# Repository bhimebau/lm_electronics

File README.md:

# lm_electronics
Light monitor device for hoosier national forest

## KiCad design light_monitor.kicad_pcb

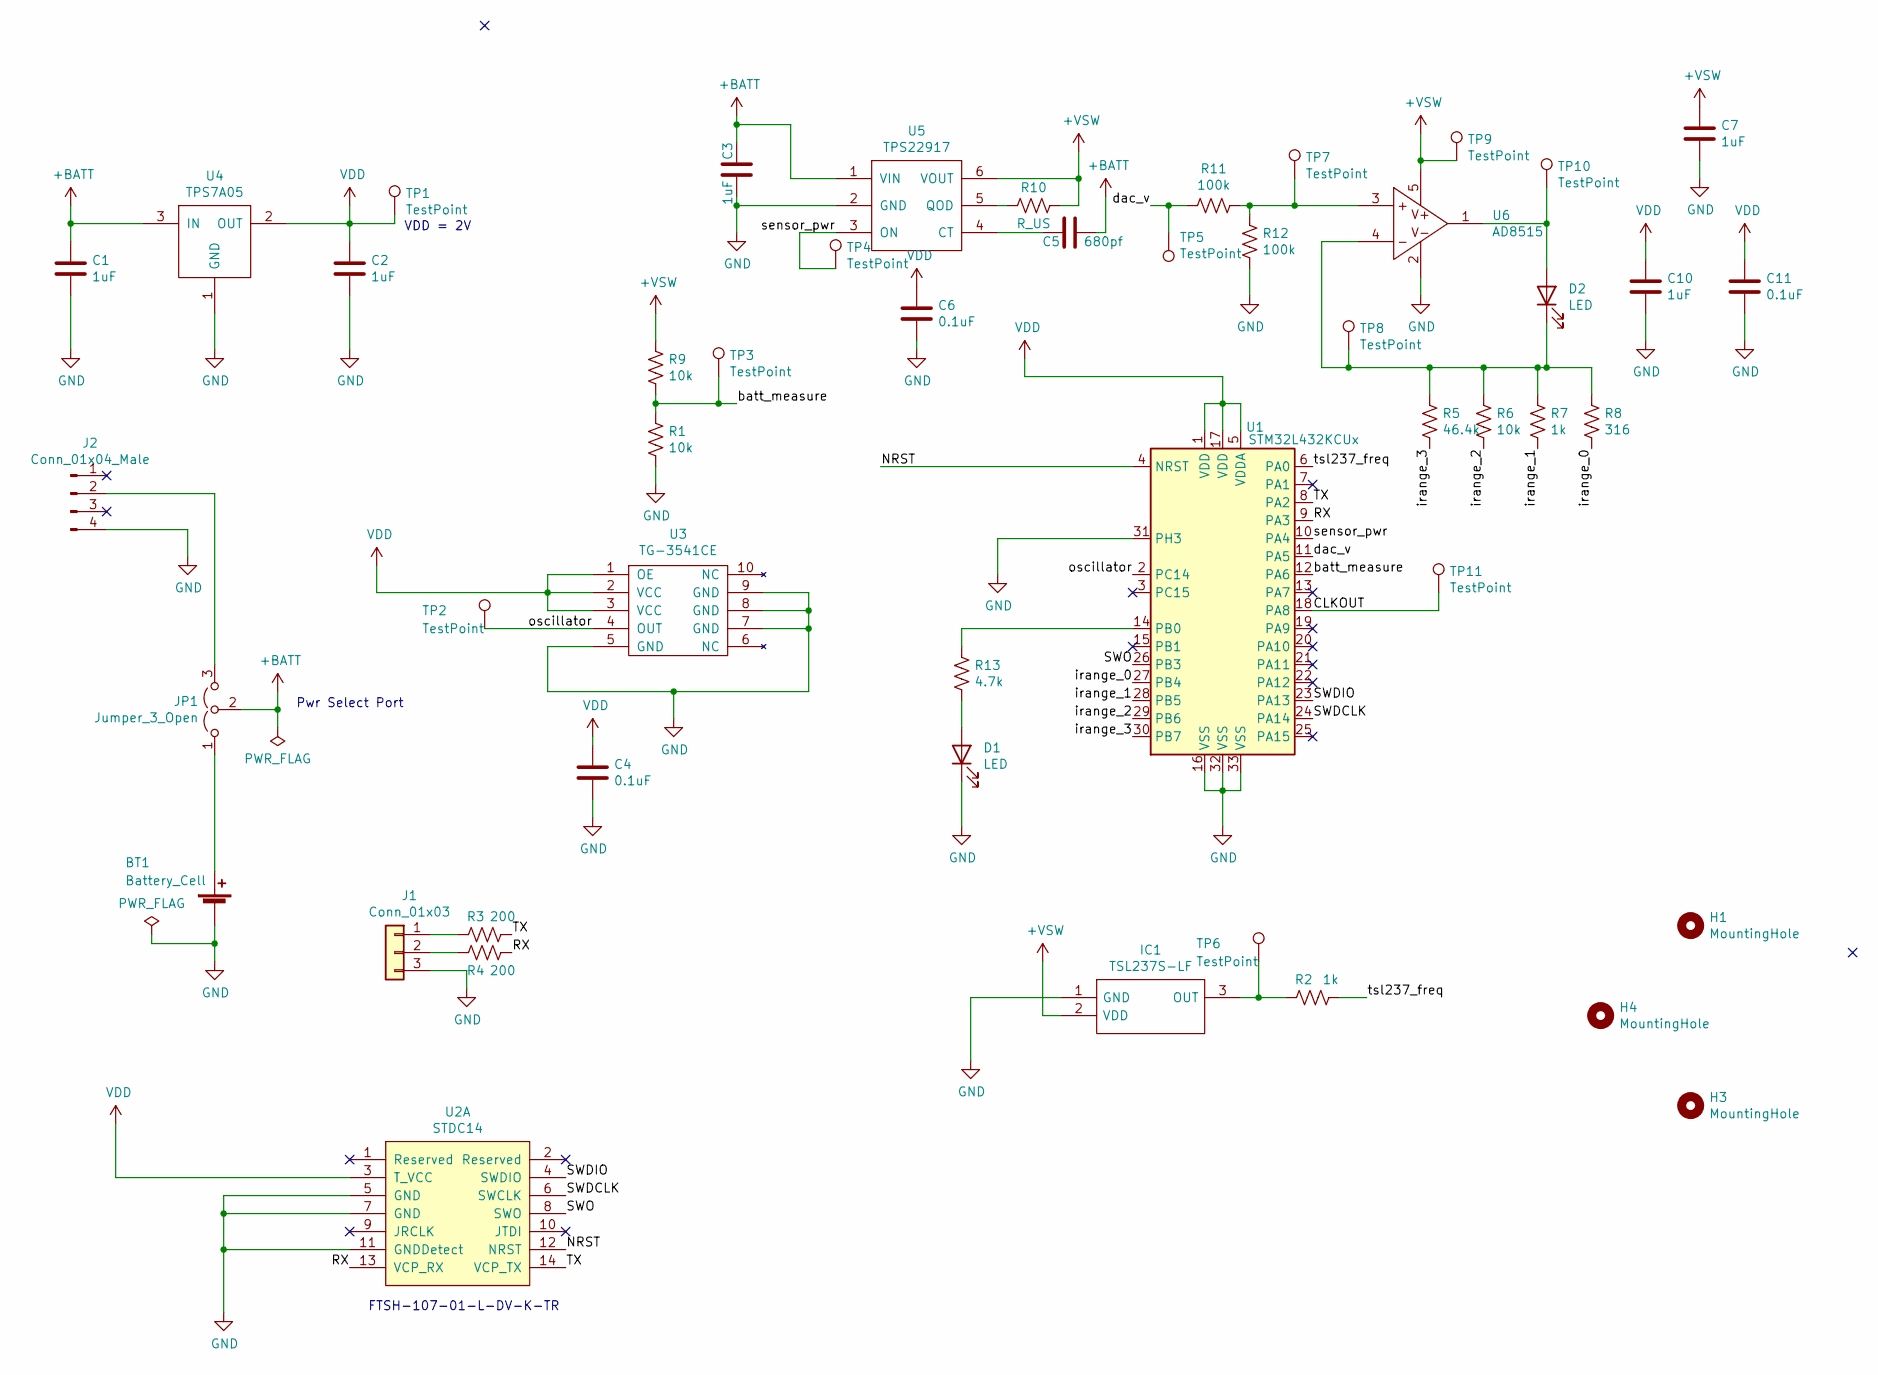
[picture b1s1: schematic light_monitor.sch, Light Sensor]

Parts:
BT1: Battery_Cell; TLH-5935
C1, C2, C3, C7, C10: 1uF; C_0603_1608Metric_Pad1.05x0.95mm_HandSolder
C4, C6, C11: 0.1uF; C_0603_1608Metric_Pad1.05x0.95mm_HandSolder
C5: 680pf; C_0603_1608Metric_Pad1.05x0.95mm_HandSolder
D1, D2: LED; LED_0603_1608Metric_Pad1.05x0.95mm_HandSolder
H1, H3, H4: MountingHole; MountingHole_2.2mm_M2_Pad_Via
IC1: TSL237S-LF; Mouser Part Number 856-TSL237S-LF
J1: Conn_01x03; JST_XH_B3B-XH-A_1x03_P2.50mm_Vertical
J2: Conn_01x04_Male; JST_XH_B4B-XH-A_1x04_P2.50mm_Vertical
JP1: Jumper_3_Open; SolderJumper-3_P1.3mm_Open_RoundedPad1.0x1.5mm
R1, R6, R9: 10k; R_0603_1608Metric_Pad1.05x0.95mm_HandSolder
R2, R7: 1k; R_0603_1608Metric_Pad1.05x0.95mm_HandSolder
R3, R4: 200; R_0603_1608Metric_Pad1.05x0.95mm_HandSolder
R5: 46.4k; R_0603_1608Metric_Pad1.05x0.95mm_HandSolder
R8: 316; R_0603_1608Metric_Pad1.05x0.95mm_HandSolder
R10: R_US; R_0603_1608Metric_Pad1.05x0.95mm_HandSolder
R11, R12: 100k; R_0603_1608Metric_Pad1.05x0.95mm_HandSolder
R13: 4.7k; R_0603_1608Metric_Pad1.05x0.95mm_HandSolder
TP1, TP2, TP3, TP4, TP5, TP6, TP7, TP8, TP9, TP10, TP11: TestPoint; TestPoint_Pad_D1.5mm
U1: STM32L432KCUx; QFN-32-1EP_5x5mm_P0.5mm_EP3.6x3.6mm
U2: STDC14; ftsh_14p_connector
U3: TG-3541CE
U4: TPS7A05; SOT-23
U5: TPS22917; SOT-23-6_Handsoldering
U6: AD8515; SOT-353_SC-70-5_Handsoldering

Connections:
+BATT: C1.1, C3.1, C5.2, JP1.2 (C), U4.3 (IN), U5.1 (VIN)
+VSW: C7.1, IC1.2 (VDD), R9.1, R10.2, TP9.1, U5.6 (VOUT), U6.5
/CLKOUT: TP11.1, U1.18 (PA8)
/NRST: U1.4 (NRST), U2.12 (NRST)
/RX: R4.1, U1.9 (PA3), U2.13 (VCP_RX)
/SWDCLK: U1.24 (PA14), U2.6 (SWCLK)
/SWDIO: U1.23 (PA13), U2.4 (SWDIO)
/SWO: U1.26 (PB3), U2.8 (SWO)
/TX: R3.1, U1.8 (PA2), U2.14 (VCP_TX)
/batt_measure: R1.1, R9.2, TP3.1, U1.12 (PA6)
/dac_v: R11.2, TP5.1, U1.11 (PA5)
/irange_0: R8.2, U1.27 (PB4)
/irange_1: R7.2, U1.28 (PB5)
/irange_2: R6.2, U1.29 (PB6)
/irange_3: R5.2, U1.30 (PB7)
/oscillator: TP2.1, U1.2 (PC14), U3.4 (OUT)
/sensor_pwr: TP4.1, U1.10 (PA4), U5.3 (ON)
/tsl237_freq: R2.1, U1.6 (PA0)
GND: BT1.2 (-), C1.2, C2.2, C3.2, C4.2, C6.2, C7.2, C10.2, C11.2, D1.1 (K), IC1.1 (GND), J1.3, J2.4, R1.2, R12.2, U1.16 (VSS), U1.31 (PH3), U1.32 (VSS), U1.33 (VSS), U2.5 (GND), U2.7 (GND), U2.11 (GNDDetect), U3.5 (GND), U3.7 (GND), U3.8 (GND), U3.9 (GND), U4.1 (GND), U5.2 (GND), U6.2
unnamed: BT1.1 (+), JP1.1 (A)
unnamed: C5.1, U5.4 (CT)
unnamed: D1.2 (A), R13.2
unnamed: D2.1 (K), R5.1, R6.1, R7.1, R8.1, TP8.1, U6.4
unnamed: D2.2 (A), TP10.1, U6.1
unnamed: IC1.3 (OUT), R2.2, TP6.1
unnamed: J1.1, R3.2
unnamed: J1.2, R4.2
unnamed: J2.2, JP1.3 (B)
unnamed: R10.1, U5.5 (QOD)
unnamed: R11.1, R12.1, TP7.1, U6.3
unnamed: R13.1, U1.14 (PB0)
VDD: C2.1, C4.1, C6.1, C10.1, C11.1, TP1.1, U1.1 (VDD), U1.5 (VDDA), U1.17 (VDD), U2.3 (T_VCC), U3.1 (OE), U3.2 (VCC), U3.3 (VCC), U4.2 (OUT)

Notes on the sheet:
FTSH-107-01-L-DV-K-TR
Pwr Select Port
VDD = 2V

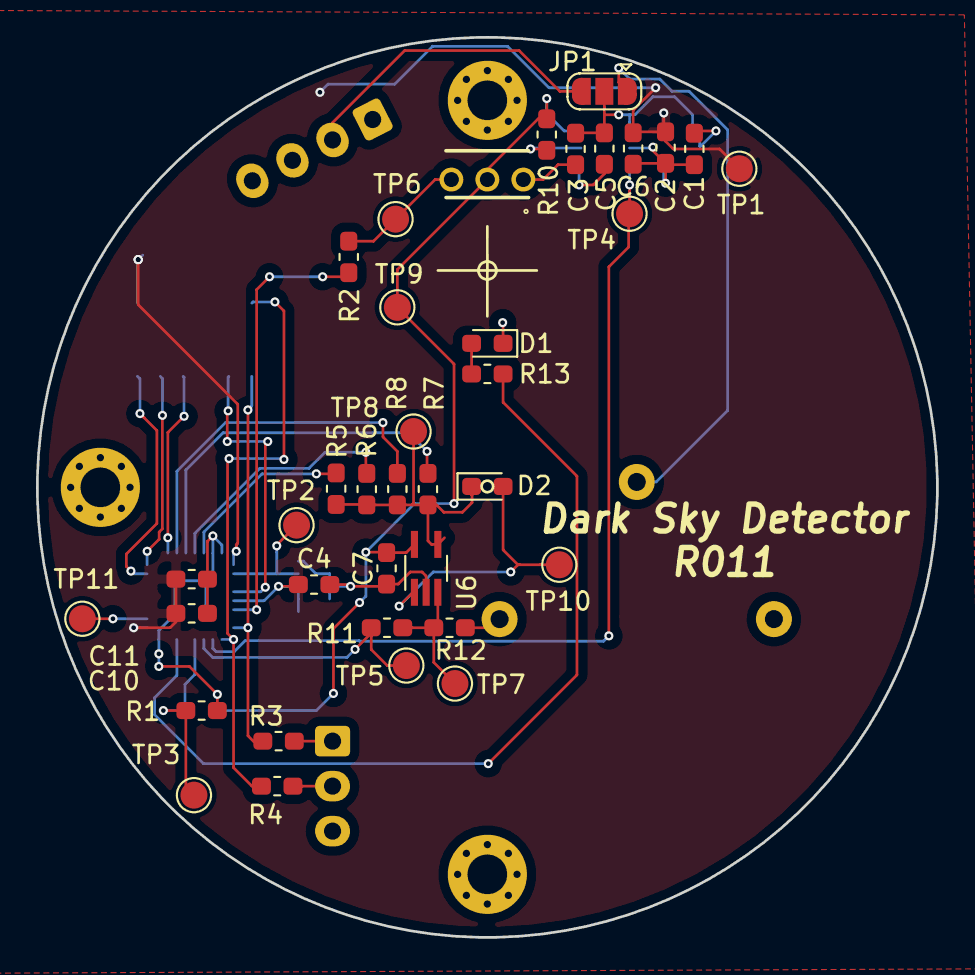
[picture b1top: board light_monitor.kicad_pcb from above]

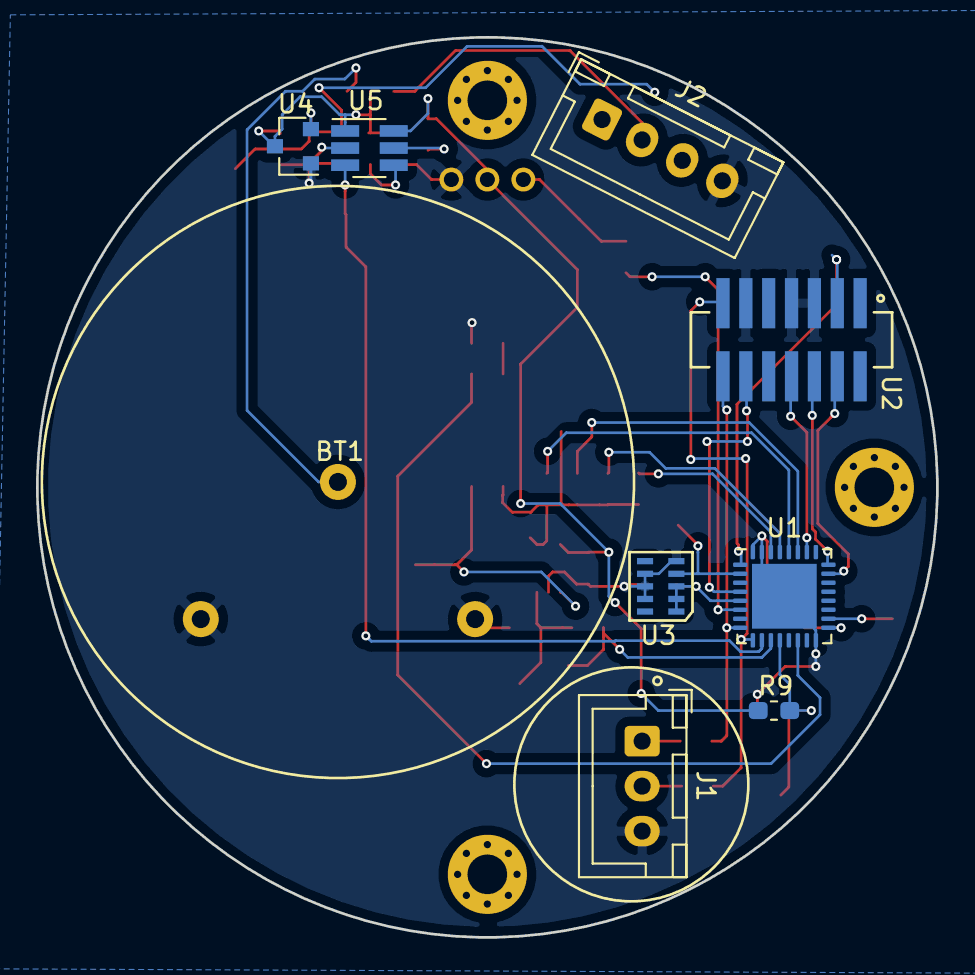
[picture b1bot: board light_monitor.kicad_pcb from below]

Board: 2 copper layers, 50.0 x 50.0 mm, 49 parts (9 on the bottom side), 32 nets.

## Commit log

2019-02-23 added everthing
2019-02-26 R001 ordered from osh
2019-02-26 removed unused files
2019-02-26 light monitor added
2019-02-28 added boot jumper
2019-02-28 breakout r001 complete
2019-02-28 checkpoint
2019-03-03 added changes to the jtag connector
2019-03-10 beginning the process of cleaning up the pad issues
2019-03-21 completed r002 board - shipped
2019-03-21 updated software dev board
2019-03-29 added power shield manual
2019-05-28 ordered r003 software boards
2019-06-07 sensor complete
2019-06-28 added logo to the repo
2019-07-16 checking rev 4
2019-07-17 r004 board added
2019-07-18 breakout completed
2019-07-21 r004 breakout created and routed.
2019-07-22 changed title block
2019-07-23 updated the breakout project
2019-07-23 added a doc on how to handle vbus
2019-07-29 rev 005 lpuart sent to macrofab
2019-08-06 r006 sensor committed
2019-08-06 not sure what changed
2019-09-12 checkin for rev 6
2019-11-12 added version 7 parts
2019-11-12 completed and ordered version 7 of the board
2020-01-23 pushing off r007
2020-01-25 revision 8 sent to fab
2020-02-07 sent to fab
2020-02-10 saved off r009
2020-03-05 rev 10 board
2020-03-13 added the version used by the students
2020-03-23 added corrected values for caps and resistor
2020-04-03 r010 build
2020-04-13 added schematic with values from debug:
2020-05-18 board with lipo battery
2020-06-24 save off before access from freecad
2020-11-11 added all changed files
2022-01-30 checkpoint for kicad 6
